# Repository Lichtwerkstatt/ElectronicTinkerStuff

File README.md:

# ElectronicTinkerStuff
A little Repository with all our small electronic projects

## PCBs
**All circuit boards are available for free use under the MIT License. If you use them directly without significant modifications, I would simply ask that you leave the name of the organization (Lichtwerkstatt) and the designer (Canan Gallitschke) on the circuit boards.**

A collection of all our self-designed PCBs. Included for each PCB are:
- KiCad files
- SVG graphics
- Gerber files for JLCPCB

The “footprints” folder contains all custom footprints. 

The Excel file “Teileliste.xls” contains a list of the required components and purchase links for most PCBs.

For each board, there is a “production” folder containing a ZIP file with the Gerber files. This ZIP file can be uploaded directly to JLCPCB for production.

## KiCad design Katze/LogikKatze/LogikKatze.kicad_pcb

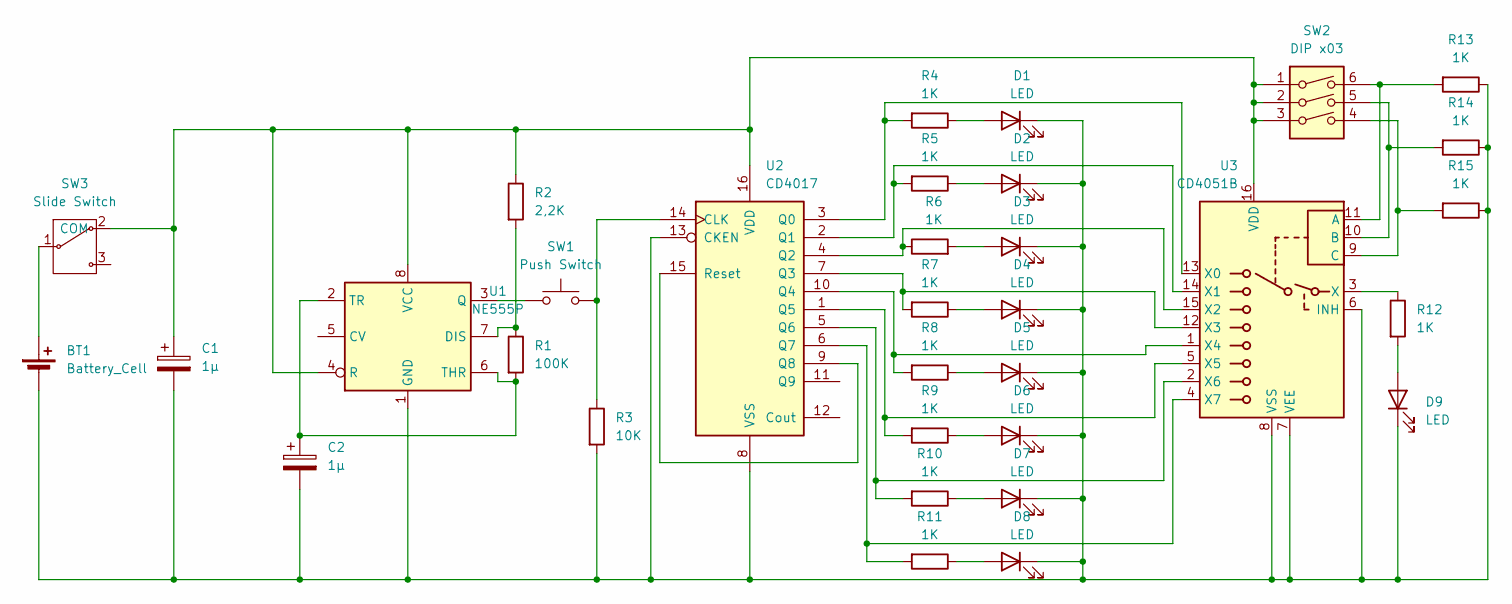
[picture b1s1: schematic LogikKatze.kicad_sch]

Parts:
BT1: Battery_Cell; Battery_MPD_BHX2-2032-PC_2x2032
C1, C2: 1µ; CP_Radial_D5.0mm_P2.00mm
D1, D2, D3, D4, D5, D6, D7, D8, D9: LED; LED_D3.0mm
R1: 100K; R_Axial_DIN0207_L6.3mm_D2.5mm_P10.16mm_Horizontal
R2: 2,2K; R_Axial_DIN0207_L6.3mm_D2.5mm_P10.16mm_Horizontal
R3: 10K; R_Axial_DIN0207_L6.3mm_D2.5mm_P10.16mm_Horizontal
R4, R5, R6, R7, R8, R9, R10, R11, R12, R13, R14, R15: 1K; R_Axial_DIN0207_L6.3mm_D2.5mm_P10.16mm_Horizontal
SW1: Push Switch; SW_PUSH_6mm
SW2: DIP x03; SW_DIP_SPSTx03_Slide_9.78x9.8mm_W7.62mm_P2.54mm
SW3: Slide Switch; Slide Switch True Components
U1: NE555P; DIP-8_W7.62mm
U2: CD4017; CERDIP-16_W7.62mm_SideBrazed_Socket
U3: CD4051B; CERDIP-16_W7.62mm_SideBrazed_Socket

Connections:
unnamed: BT1.1 (+), SW3.1
unnamed: BT1.2 (-), C1.2, C2.2, D1.1 (K), D2.1 (K), D3.1 (K), D4.1 (K), D5.1 (K), D6.1 (K), D7.1 (K), D8.1 (K), D9.1 (K), R3.2, R13.1, R14.1, R15.1, U1.1 (GND), U2.8 (VSS), U2.13 (CKEN), U3.6 (INH), U3.7 (VEE), U3.8 (VSS)
unnamed: D1.2 (A), R4.1
unnamed: D2.2 (A), R5.1
unnamed: D3.2 (A), R6.2
unnamed: D4.2 (A), R7.1
unnamed: D5.2 (A), R8.1
unnamed: D6.2 (A), R9.1
unnamed: D7.2 (A), R10.1
unnamed: D8.2 (A), R11.1
unnamed: D9.2 (A), R12.2
unnamed: C1.1, R2.1, SW2.1, SW2.2, SW2.3, SW3.2 (COM), U1.4 (R), U1.8 (VCC), U2.16 (VDD), U3.16 (VDD)
unnamed: R1.1, R2.2, U1.7 (DIS)
unnamed: SW1.1, U1.3 (Q)
unnamed: C2.1, R1.2, U1.2 (TR), U1.6 (THR)
unnamed: R3.1, SW1.2, U2.14 (CLK)
unnamed: R4.2, U2.3 (Q0), U3.13 (X0)
unnamed: R5.2, U2.2 (Q1), U3.14 (X1)
unnamed: R6.1, U2.4 (Q2), U3.15 (X2)
unnamed: R7.2, U2.7 (Q3), U3.12 (X3)
unnamed: R8.2, U2.10 (Q4), U3.1 (X4)
unnamed: R9.2, U2.1 (Q5), U3.5 (X5)
unnamed: R10.2, U2.5 (Q6), U3.2 (X6)
unnamed: R11.2, U2.6 (Q7), U3.4 (X7)
unnamed: U2.9 (Q8), U2.15 (Reset)
unnamed: R13.2, SW2.6, U3.11 (A)
unnamed: R14.2, SW2.5, U3.10 (B)
unnamed: R15.2, SW2.4, U3.9 (C)
unnamed: R12.1, U3.3 (X)

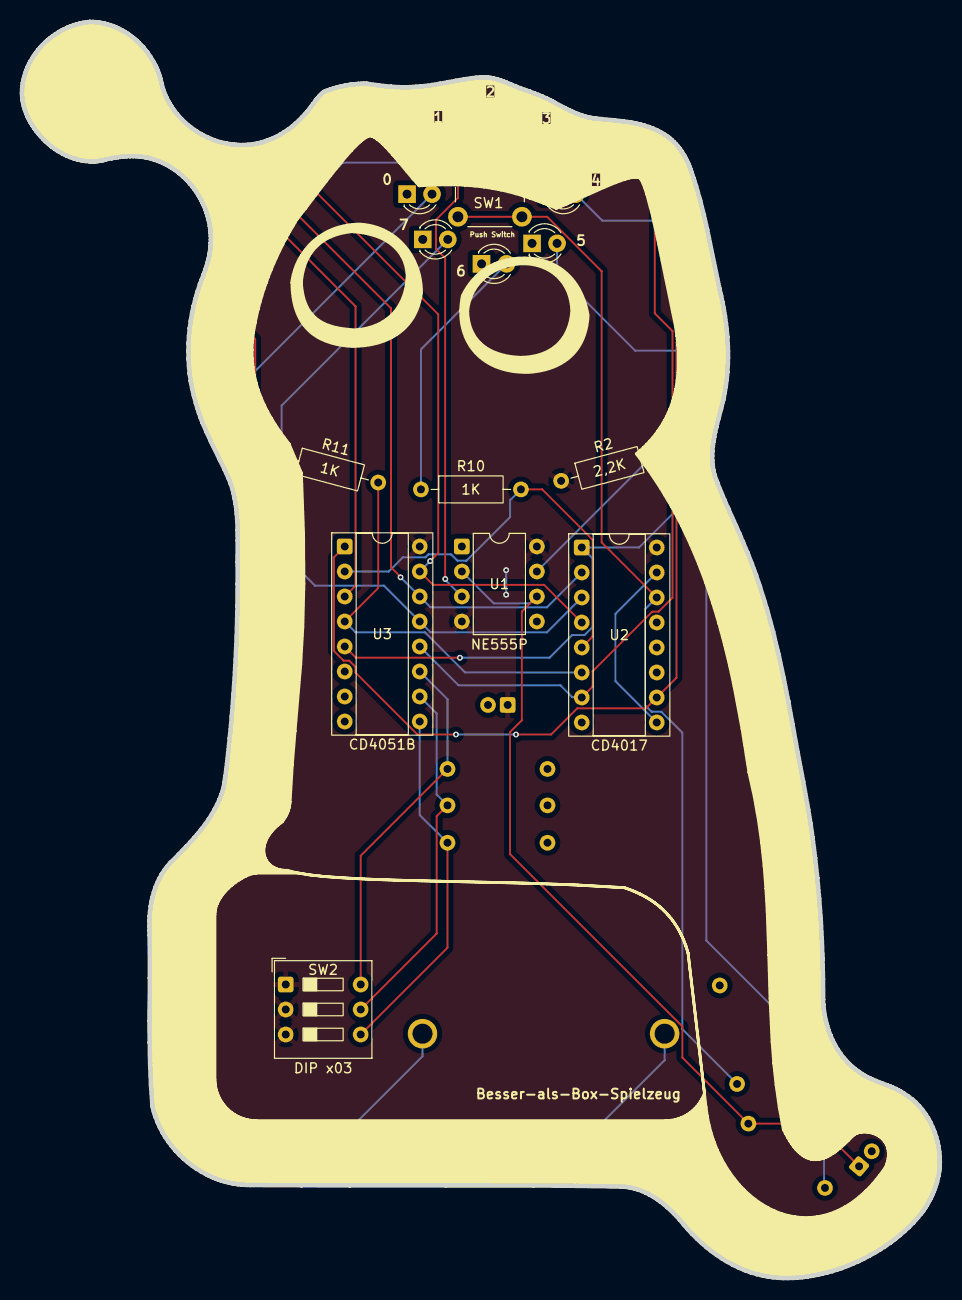
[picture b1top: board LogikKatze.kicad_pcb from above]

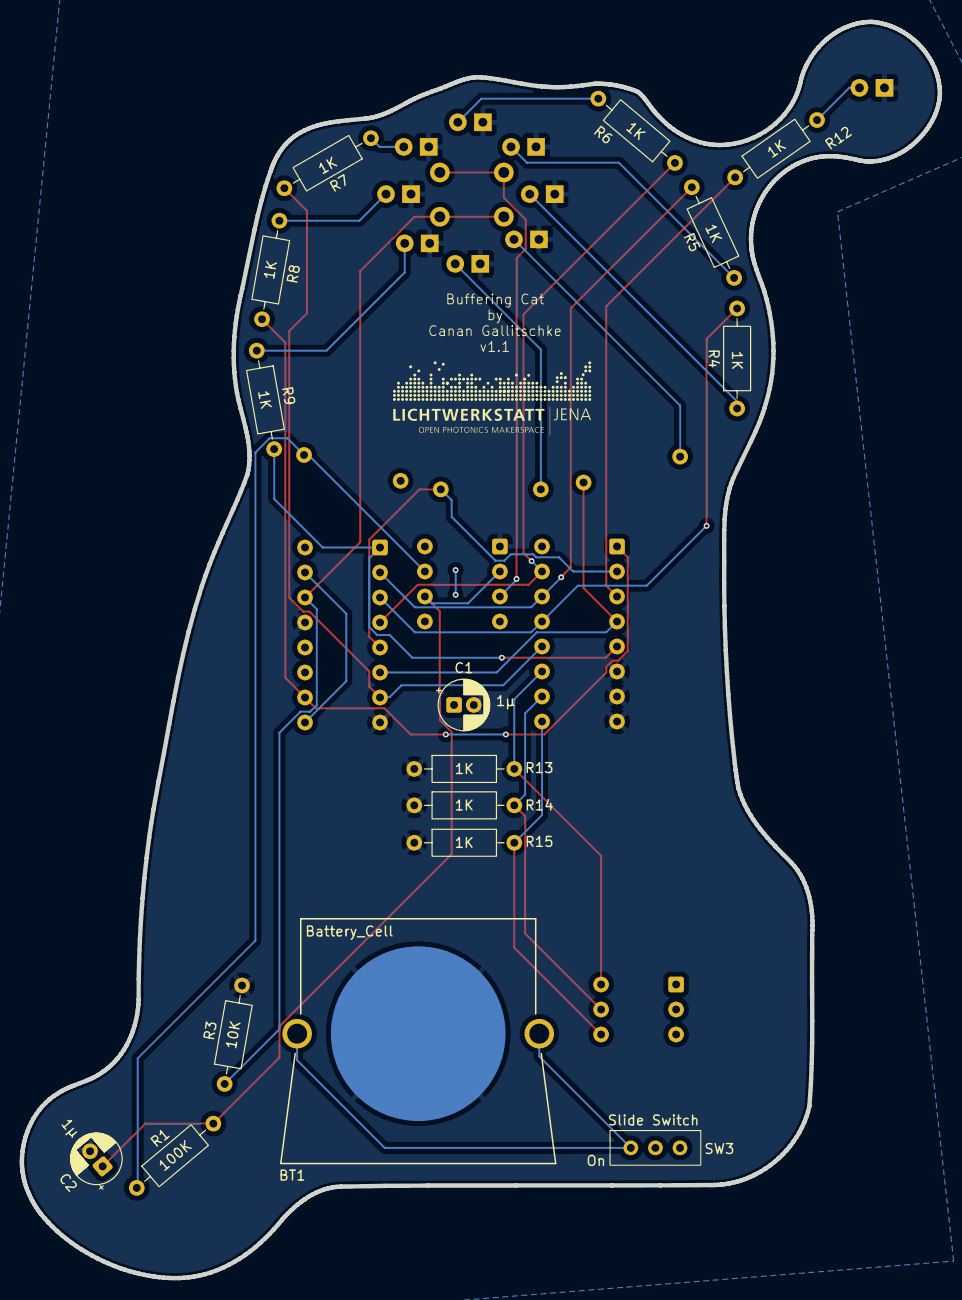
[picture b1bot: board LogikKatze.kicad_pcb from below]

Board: 2 copper layers, 93.3 x 127.6 mm, 33 parts (16 on the bottom side), 29 nets.

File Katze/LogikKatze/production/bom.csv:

Designator,Footprint,Quantity,Value,LCSC Part #
BT1,Battery_MPD_BHX2-2032-PC_2x2032,1,Battery_Cell,
"C1, C2",CP_Radial_D5.0mm_P2.00mm,2,1µ,
"D1, D2, D3, D4, D5, D6, D7, D8, D9",LED_D3.0mm,9,LED,
R1,R_Axial_DIN0207_L6.3mm_D2.5mm_P10.16mm_Horizontal,1,100K,
"R10, R11, R12, R13, R14, R15, R4, R5, R6, R7, R8, R9",R_Axial_DIN0207_L6.3mm_D2.5mm_P10.16mm_Horizontal,12,1K,
R2,R_Axial_DIN0207_L6.3mm_D2.5mm_P10.16mm_Horizontal,1,"2,2K",
R3,R_Axial_DIN0207_L6.3mm_D2.5mm_P10.16mm_Horizontal,1,10K,
SW1,SW_PUSH_6mm,1,Push Switch,
SW2,SW_DIP_SPSTx03_Slide_9.78x9.8mm_W7.62mm_P2.54mm,1,DIP x03,
SW3,Slide Switch True Components,1,Slide Switch,
U1,DIP-8_W7.62mm,1,NE555P,
U2,CERDIP-16_W7.62mm_SideBrazed_Socket,1,CD4017,
U3,CERDIP-16_W7.62mm_SideBrazed_Socket,1,CD4051B,

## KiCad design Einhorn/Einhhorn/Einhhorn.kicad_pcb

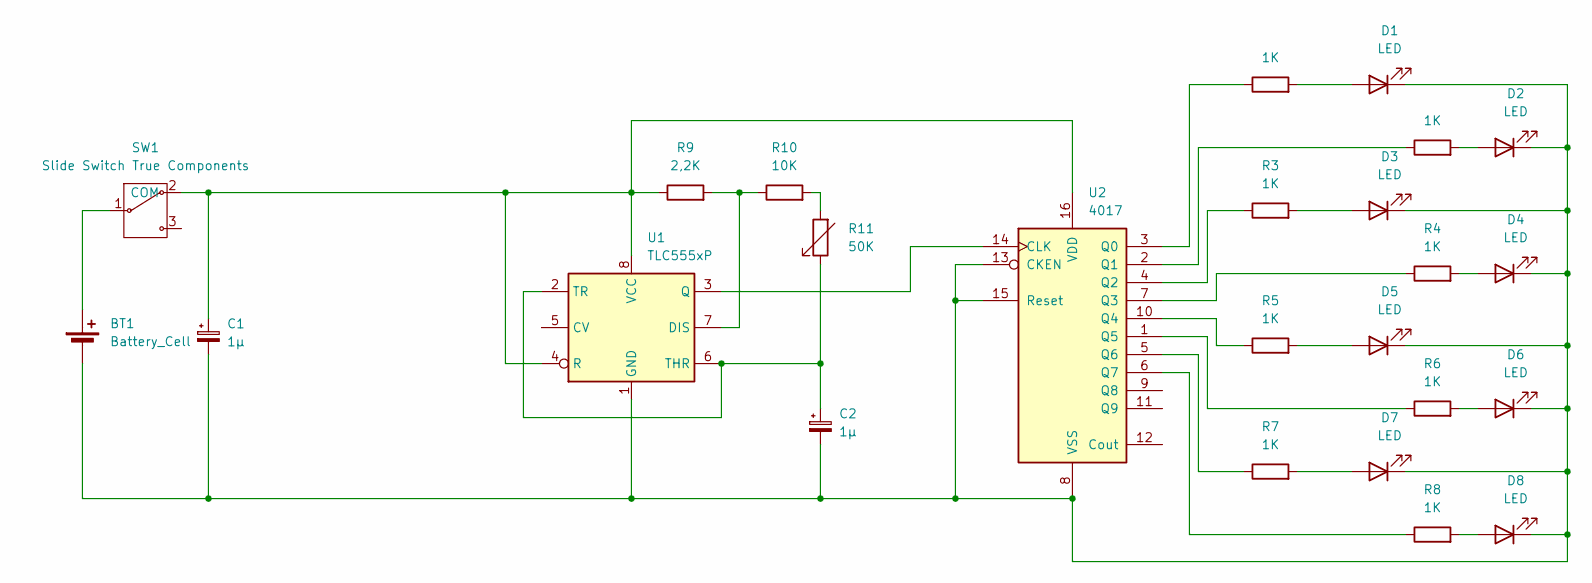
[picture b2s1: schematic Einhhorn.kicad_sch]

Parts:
BT1: Battery_Cell; Battery_MPD_BHX2-2032-PC_2x2032
C1, C2: 1µ; CP_Axial_L11.0mm_D5.0mm_P18.00mm_Horizontal
D1, D2, D3, D4, D5, D6, D7, D8: LED; LED_D5.0mm
R1, R2, R3, R4, R5, R6, R7, R8: 1K; R_Axial_DIN0207_L6.3mm_D2.5mm_P10.16mm_Horizontal
R9: 2,2K; R_Axial_DIN0207_L6.3mm_D2.5mm_P10.16mm_Horizontal
R10: 10K; R_Axial_DIN0207_L6.3mm_D2.5mm_P10.16mm_Horizontal
R11: 50K; Potentiometer_Weltron_CA6-V5_Vertical
SW1: Slide Switch True Components
U1: TLC555xP; DIP-8_W7.62mm_Socket
U2: 4017; CERDIP-16_W7.62mm_SideBrazed_Socket

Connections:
unnamed: BT1.1 (+), SW1.1
unnamed: BT1.2 (-), C1.2, C2.2, D1.1 (K), D2.1 (K), D3.1 (K), D4.1 (K), D5.1 (K), D6.1 (K), D7.1 (K), D8.1 (K), U1.1 (GND), U2.8 (VSS), U2.13 (CKEN), U2.15 (Reset)
unnamed: D1.2 (A), R1.2
unnamed: D2.2 (A), R2.2
unnamed: D3.2 (A), R3.2
unnamed: D4.2 (A), R4.2
unnamed: D5.2 (A), R5.2
unnamed: D6.2 (A), R6.2
unnamed: D7.2 (A), R7.2
unnamed: D8.2 (A), R8.2
unnamed: R10.2, R11.2
unnamed: C1.1, R9.1, SW1.2 (COM), U1.4 (R), U1.8 (VCC), U2.16 (VDD)
unnamed: R9.2, R10.1, U1.7 (DIS)
unnamed: U1.3 (Q), U2.14 (CLK)
unnamed: C2.1, R11.1, U1.2 (TR), U1.6 (THR)
unnamed: R1.1, U2.3 (Q0)
unnamed: R2.1, U2.2 (Q1)
unnamed: R3.1, U2.4 (Q2)
unnamed: R4.1, U2.7 (Q3)
unnamed: R5.1, U2.10 (Q4)
unnamed: R6.1, U2.1 (Q5)
unnamed: R7.1, U2.5 (Q6)
unnamed: R8.1, U2.6 (Q7)

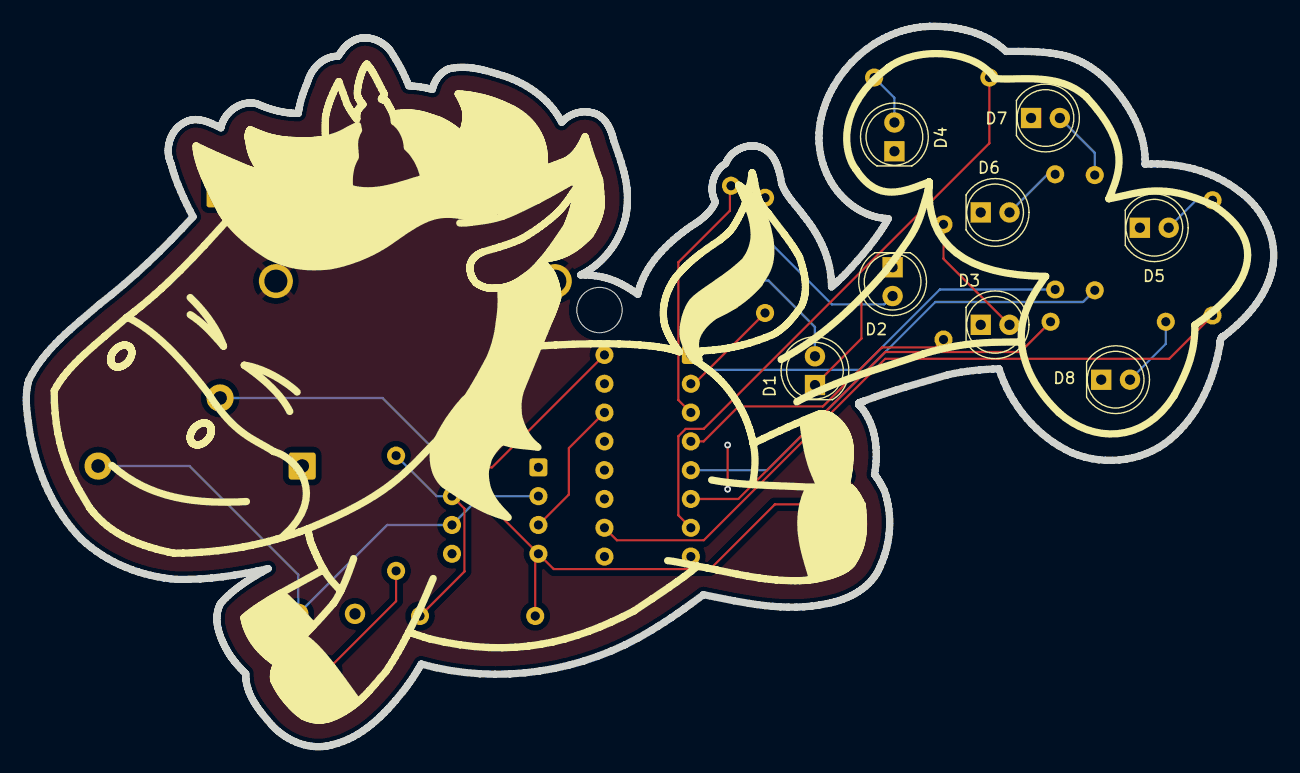
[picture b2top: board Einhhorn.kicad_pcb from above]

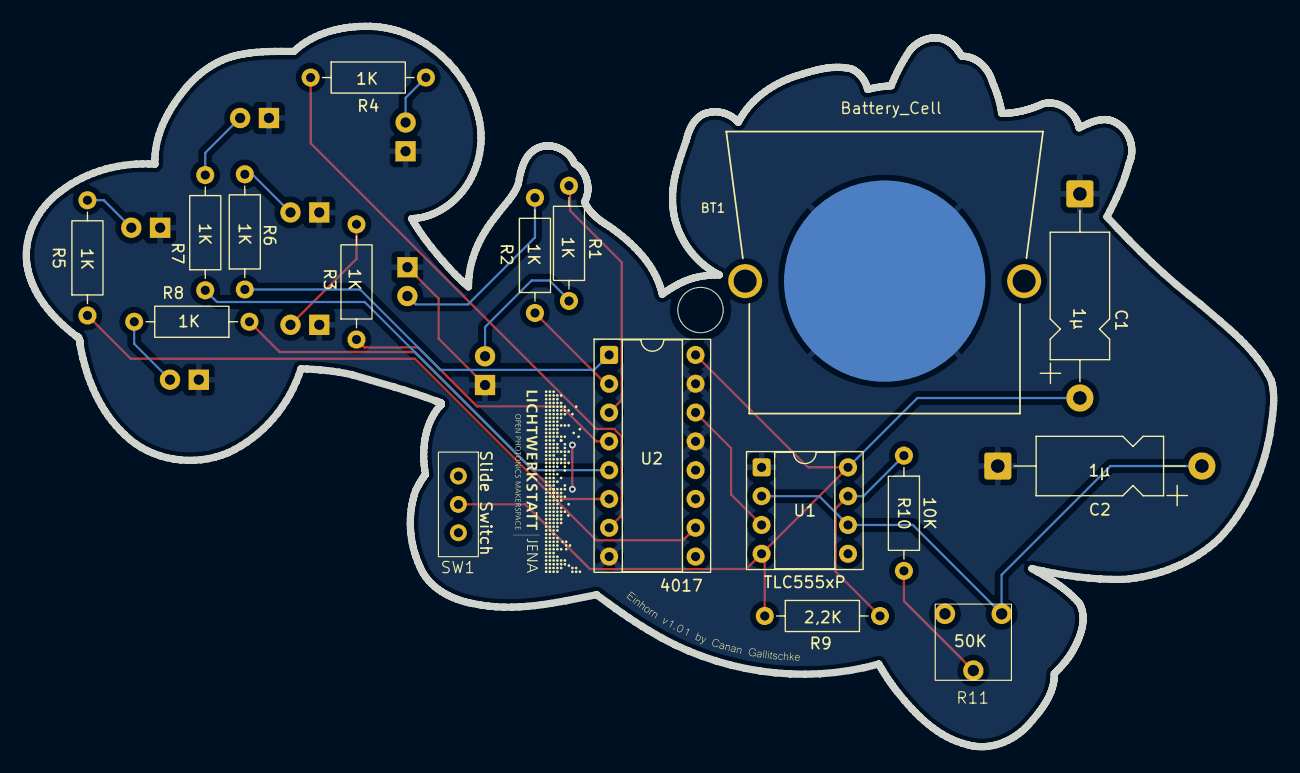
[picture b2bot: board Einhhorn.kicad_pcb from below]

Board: 2 copper layers, 110.0 x 63.5 mm, 25 parts (17 on the bottom side), 23 nets.

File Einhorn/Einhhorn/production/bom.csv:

Designator,Footprint,Quantity,Value,LCSC Part #
BT1,Battery_MPD_BHX2-2032-PC_2x2032,1,Battery_Cell,
"C1, C2",CP_Axial_L11.0mm_D5.0mm_P18.00mm_Horizontal,2,1µ,
"D1, D2, D3, D4, D5, D6, D7, D8",LED_D5.0mm,8,LED,
"R1, R2, R3, R4, R5, R6, R7, R8",R_Axial_DIN0207_L6.3mm_D2.5mm_P10.16mm_Horizontal,8,1K,
R10,R_Axial_DIN0207_L6.3mm_D2.5mm_P10.16mm_Horizontal,1,10K,
R11,Potentiometer_Weltron_CA6-V5_Vertical,1,50K,
R9,R_Axial_DIN0207_L6.3mm_D2.5mm_P10.16mm_Horizontal,1,"2,2K",
SW1,Slide Switch True Components,1,Slide Switch,
U1,DIP-8_W7.62mm_Socket,1,TLC555xP,
U2,CERDIP-16_W7.62mm_SideBrazed_Socket,1,4017,

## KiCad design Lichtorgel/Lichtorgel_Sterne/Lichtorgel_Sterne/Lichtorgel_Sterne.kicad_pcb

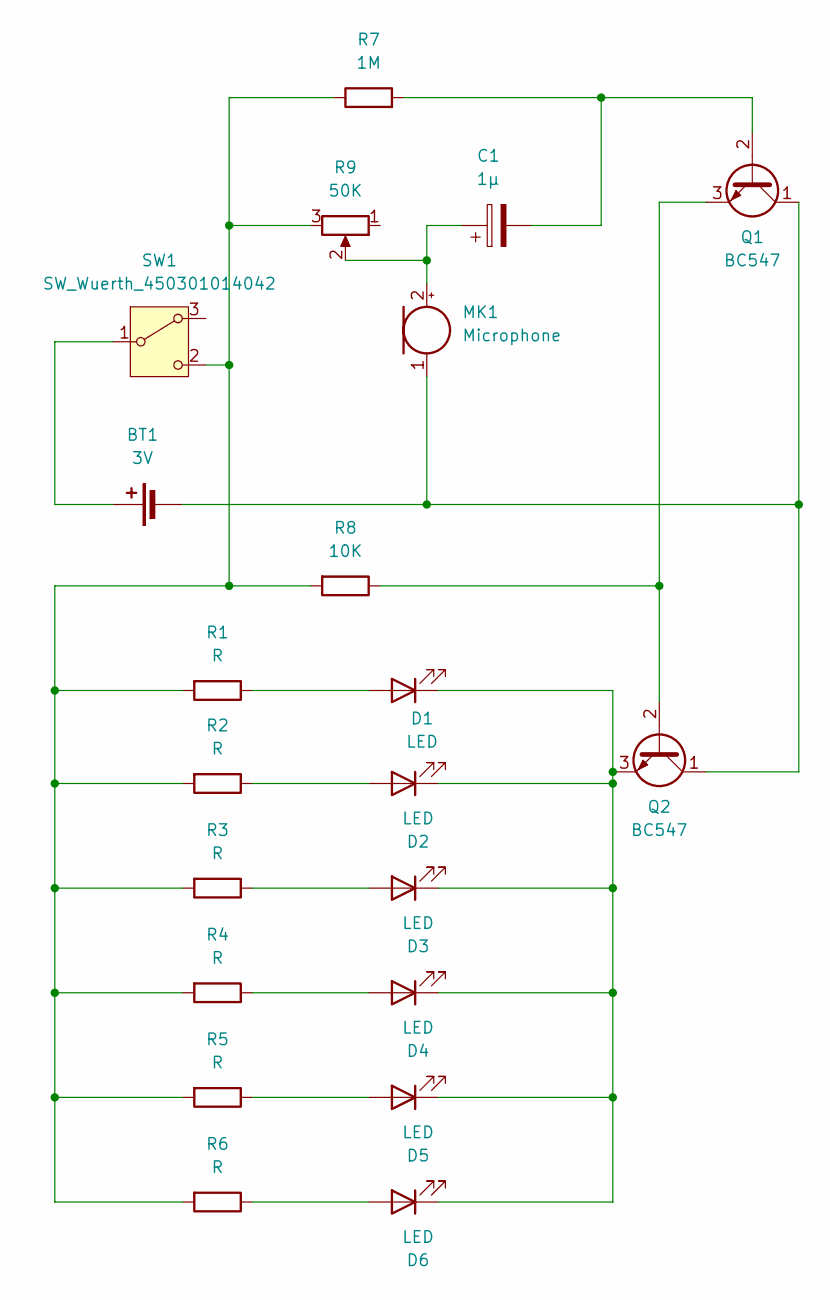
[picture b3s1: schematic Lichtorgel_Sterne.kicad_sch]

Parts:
BT1: 3V; BatteryHolder_TrueComponents_TC-13220724_2016_2020_202_2032
C1: 1µ; CP_Radial_D5.0mm_P2.00mm
D1, D2, D3: LED; LED_D5.0mm
D4, D5, D6: LED; LED_D3.0mm
MK1: Microphone; ElectretCondenserMicrophoneCapsule_EKULIT_d9.7mm_h6.5mm
Q1, Q2: BC547; TO-92_HandSolder_reversed
R1, R2, R3, R4, R5, R6: R; R_Axial_DIN0207_L6.3mm_D2.5mm_P10.16mm_Horizontal
R7: 1M; R_Axial_DIN0207_L6.3mm_D2.5mm_P10.16mm_Horizontal
R8: 10K; R_Axial_DIN0207_L6.3mm_D2.5mm_P10.16mm_Horizontal
R9: 50K; Potentiometer_Weltron_CA6-V5_Vertical
SW1: SW_Wuerth_450301014042; Slide Switch True Components

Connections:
unnamed: BT1.1 (+), SW1.1 (B)
unnamed: BT1.2 (-), MK1.1 (-), Q1.1 (C), Q2.1 (C)
unnamed: D1.2 (A), R1.1
unnamed: D1.1 (K), D2.1 (K), D3.1 (K), D4.1 (K), D5.1 (K), D6.1 (K), Q2.3 (E)
unnamed: D2.2 (A), R2.1
unnamed: D3.2 (A), R3.1
unnamed: D4.2 (A), R4.1
unnamed: D5.2 (A), R5.1
unnamed: D6.2 (A), R6.1
unnamed: C1.1, MK1.2 (+), R9.2
unnamed: C1.2, Q1.2 (B), R7.2
unnamed: Q1.3 (E), Q2.2 (B), R8.1
unnamed: R1.2, R2.2, R3.2, R4.2, R5.2, R6.2, R7.1, R8.2, R9.3, SW1.2 (C)

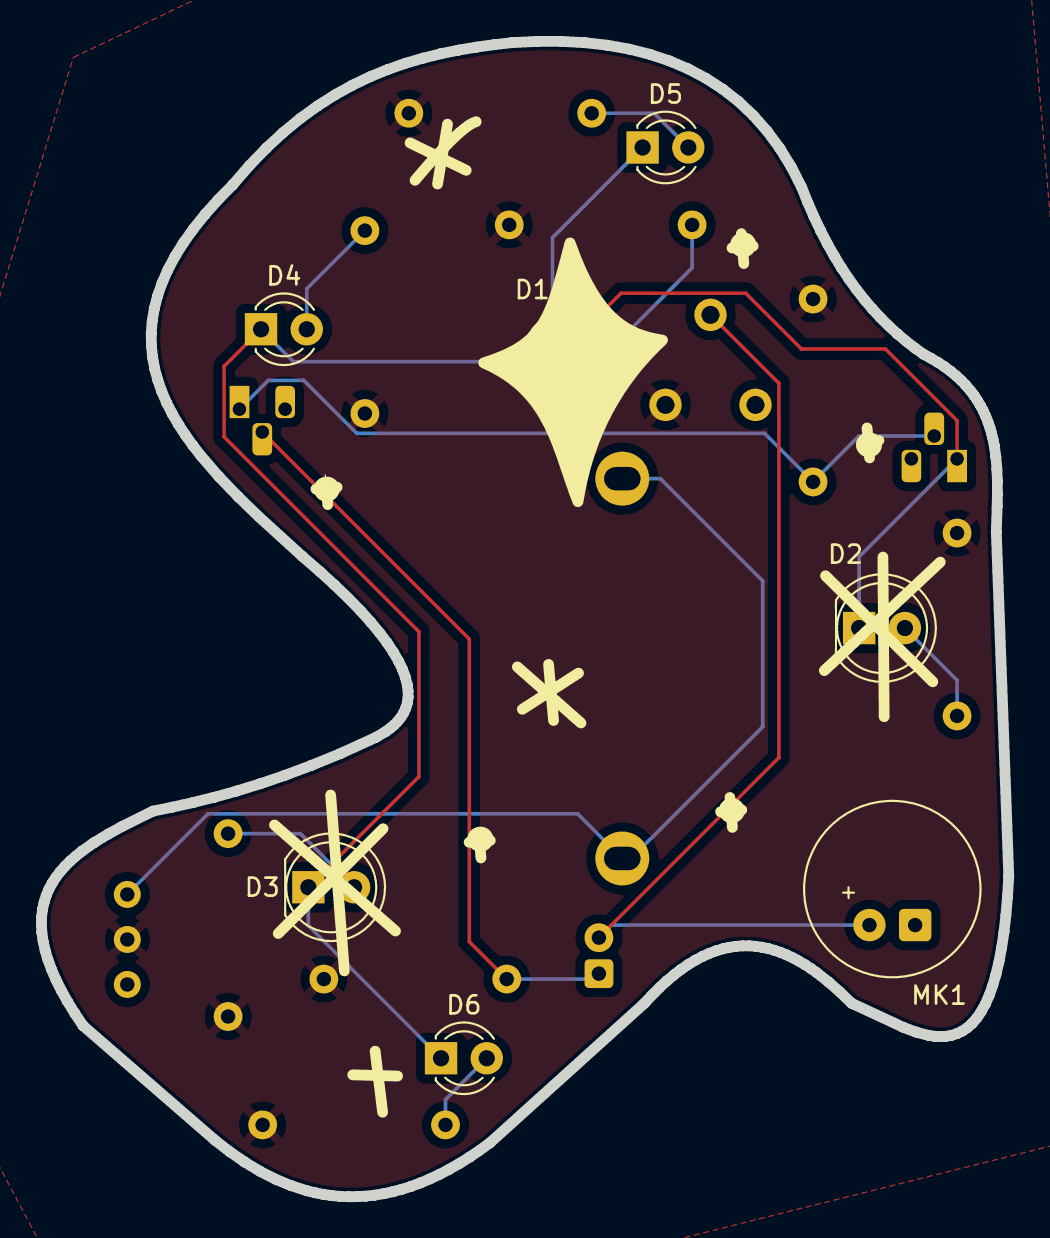
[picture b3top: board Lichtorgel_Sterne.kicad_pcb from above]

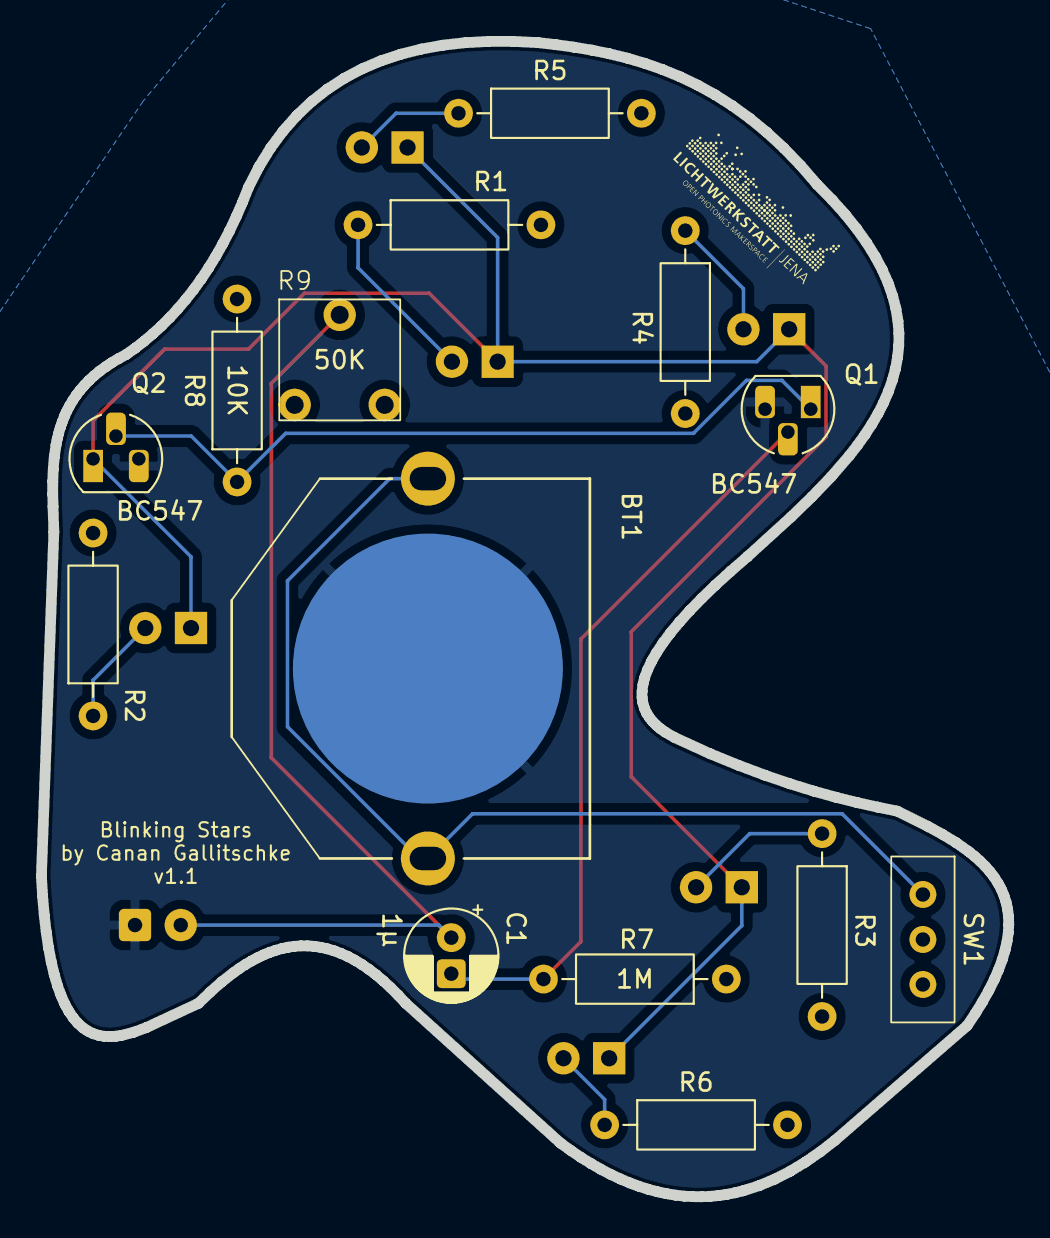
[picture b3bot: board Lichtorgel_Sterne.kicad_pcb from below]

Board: 2 copper layers, 53.7 x 64.2 mm, 21 parts (14 on the bottom side), 13 nets.

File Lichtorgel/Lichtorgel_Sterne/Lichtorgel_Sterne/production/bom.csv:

Designator,Footprint,Quantity,Value,LCSC Part #
BT1,BatteryHolder_TrueComponents_TC-13220724_2016_2020_202_2032,1,3V,
C1,CP_Radial_D5.0mm_P2.00mm,1,1µ,
"D1, D2, D3",LED_D5.0mm,3,LED,
"D4, D5, D6",LED_D3.0mm,3,LED,
MK1,ElectretCondenserMicrophoneCapsule_EKULIT_d9.7mm_h6.5mm,1,Microphone,
"Q1, Q2",TO-92_HandSolder_reversed,2,BC547,
"R1, R2, R3, R4, R5, R6",R_Axial_DIN0207_L6.3mm_D2.5mm_P10.16mm_Horizontal,6,R,
R7,R_Axial_DIN0207_L6.3mm_D2.5mm_P10.16mm_Horizontal,1,1M,
R8,R_Axial_DIN0207_L6.3mm_D2.5mm_P10.16mm_Horizontal,1,10K,
R9,Potentiometer_Weltron_CA6-V5_Vertical,1,50K,
SW1,Slide Switch True Components,1,SW_Wuerth_450301014042,

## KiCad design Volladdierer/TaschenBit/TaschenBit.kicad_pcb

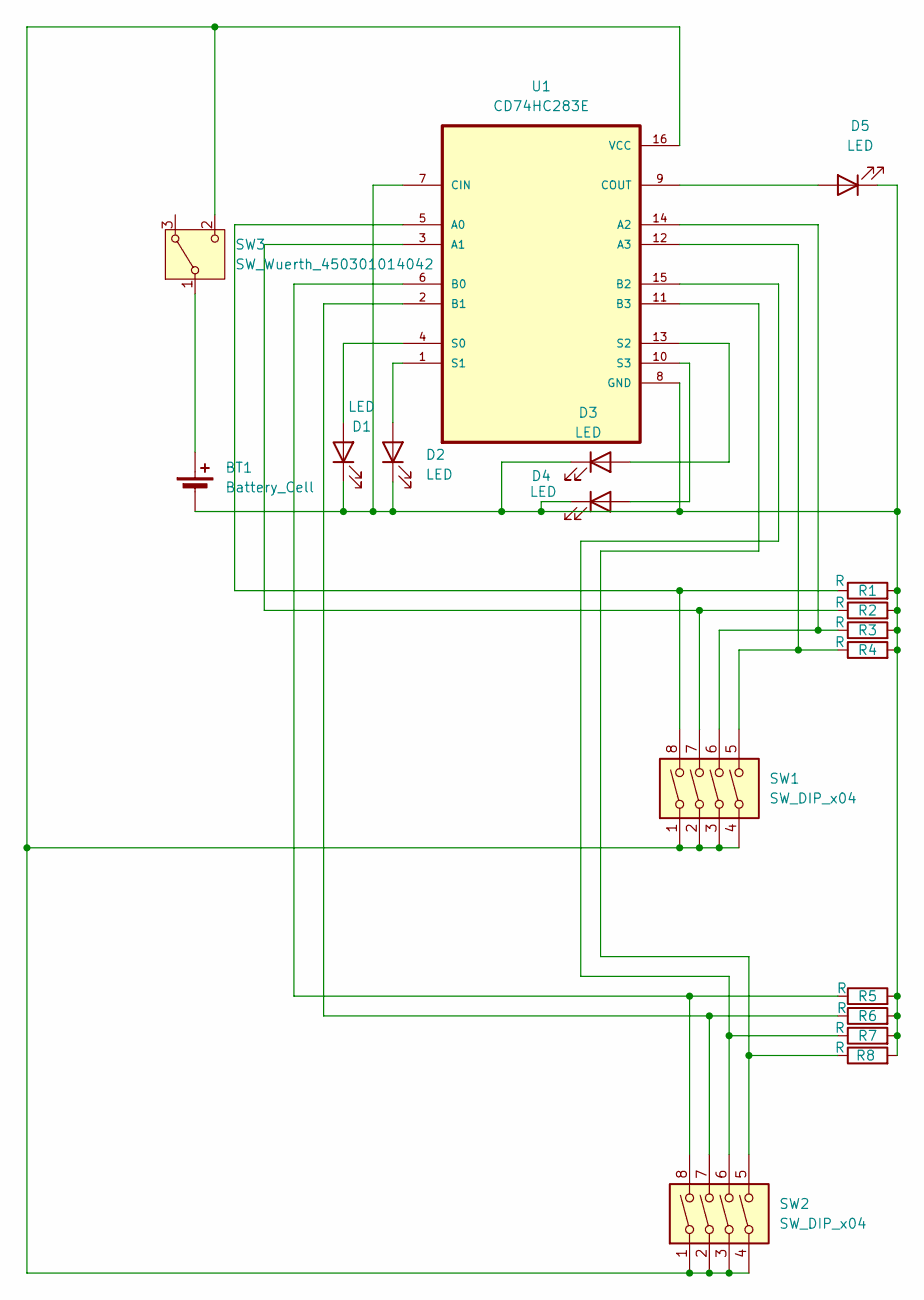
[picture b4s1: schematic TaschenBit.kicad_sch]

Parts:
BT1: Battery_Cell; BatteryHolder_TrueComponents_TC-13220724_2016_2020_202_2032
D1, D2, D3, D4, D5: LED; LED_D3.0mm
R1, R2, R3, R4, R5, R6, R7, R8: R; R_Axial_DIN0207_L6.3mm_D2.5mm_P10.16mm_Horizontal
SW1, SW2: SW_DIP_x04; DIP-8_W7.62mm_LongPads
SW3: SW_Wuerth_450301014042; Slide Switch True Components
U1: CD74HC283E; DIP-16_W7.62mm_LongPads

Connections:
unnamed: BT1.1 (+), SW3.1 (B)
unnamed: BT1.2 (-), D1.1 (K), D2.1 (K), D3.1 (K), D4.1 (K), D5.1 (K), R1.2, R2.2, R3.2, R4.2, R5.2, R6.2, R7.2, R8.2, U1.7 (CIN), U1.8 (GND)
unnamed: D1.2 (A), U1.4 (S0)
unnamed: D2.2 (A), U1.1 (S1)
unnamed: D3.2 (A), U1.13 (S2)
unnamed: D4.2 (A), U1.10 (S3)
unnamed: D5.2 (A), U1.9 (COUT)
unnamed: SW1.1, SW1.2, SW1.3, SW1.4, SW2.1, SW2.2, SW2.3, SW2.4, SW3.2 (C), U1.16 (VCC)
unnamed: R1.1, SW1.8, U1.5 (A0)
unnamed: R2.1, SW1.7, U1.3 (A1)
unnamed: R3.1, SW1.6, U1.14 (A2)
unnamed: R4.1, SW1.5, U1.12 (A3)
unnamed: R5.1, SW2.8, U1.6 (B0)
unnamed: R6.1, SW2.7, U1.2 (B1)
unnamed: R7.1, SW2.6, U1.15 (B2)
unnamed: R8.1, SW2.5, U1.11 (B3)

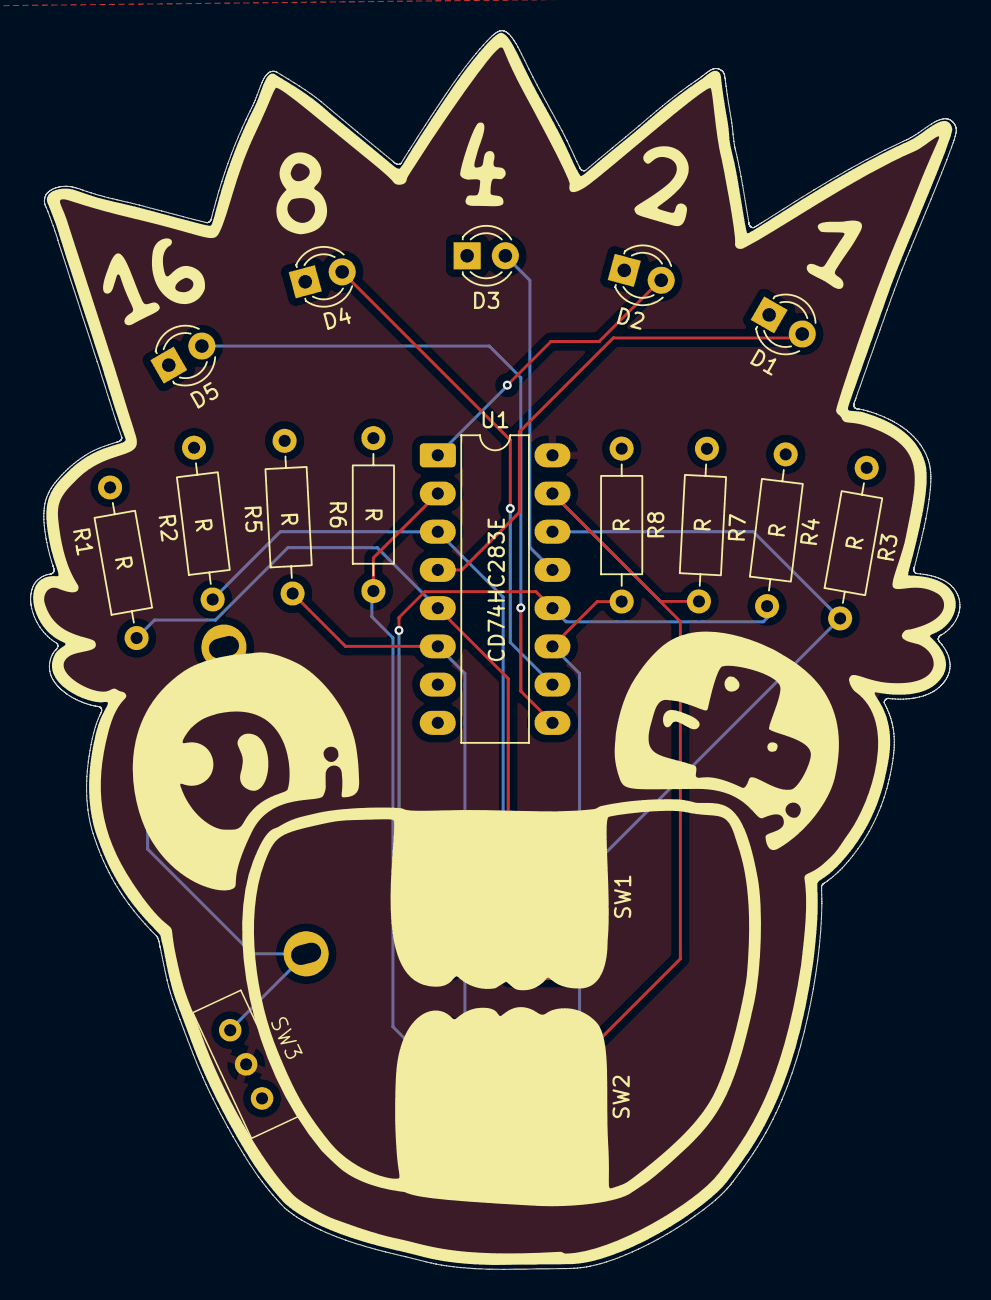
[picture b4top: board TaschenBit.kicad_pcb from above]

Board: 2 copper layers, 61.8 x 82.3 mm, 18 parts (1 on the bottom side), 16 nets.
